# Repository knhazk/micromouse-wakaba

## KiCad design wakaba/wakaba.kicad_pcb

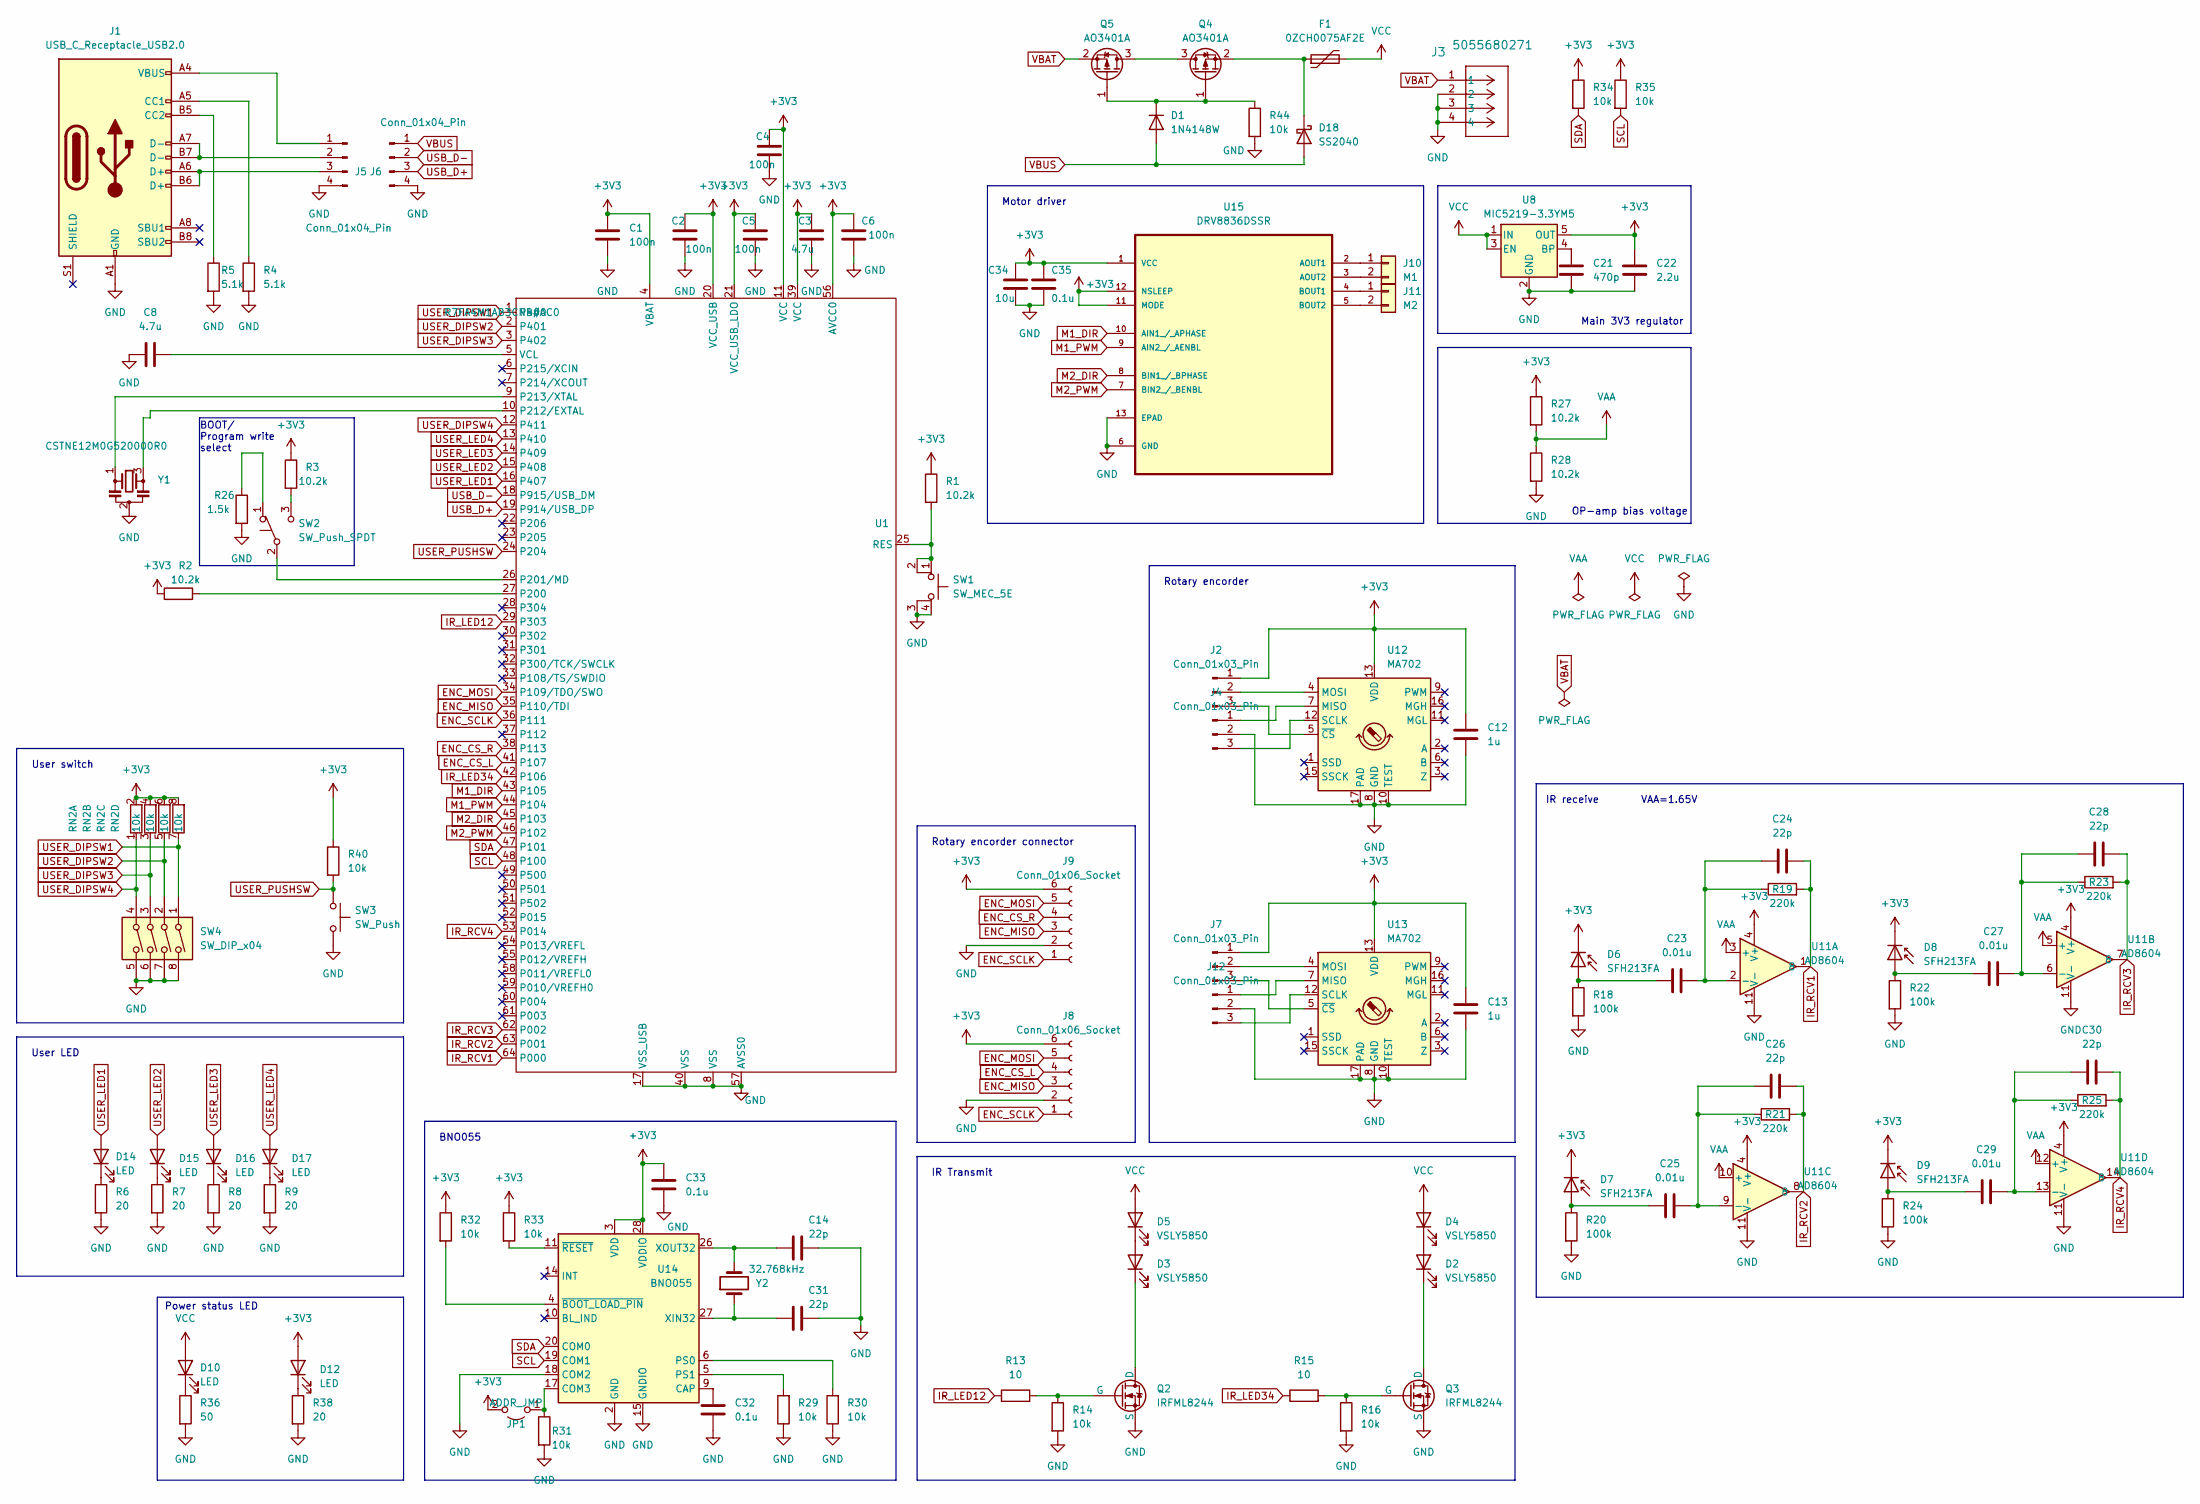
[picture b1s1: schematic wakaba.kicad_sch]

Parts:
C1, C2, C4, C5, C6: 100n; C_0603_1608Metric_Pad1.08x0.95mm_HandSolder
C3, C8: 4.7u; C_0805_2012Metric_Pad1.18x1.45mm_HandSolder
C12, C13: 1u; C_0603_1608Metric_Pad1.08x0.95mm_HandSolder
C14, C24, C26, C28, C30, C31: 22p; C_0603_1608Metric_Pad1.08x0.95mm_HandSolder
C21: 470p; C_0603_1608Metric_Pad1.08x0.95mm_HandSolder
C22: 2.2u; C_0603_1608Metric_Pad1.08x0.95mm_HandSolder
C23, C25, C27, C29: 0.01u; C_0603_1608Metric_Pad1.08x0.95mm_HandSolder
C32, C33, C35: 0.1u; C_0603_1608Metric_Pad1.08x0.95mm_HandSolder
C34: 10u; C_0603_1608Metric_Pad1.08x0.95mm_HandSolder
D1: 1N4148W; D_SOD-123
D2, D3, D4, D5: VSLY5850; LED_D5.0mm_Horizontal_O1.27mm_Z3.0mm
D6, D7, D8, D9: SFH213FA; LED_D5.0mm_Horizontal_O1.27mm_Z3.0mm
D10, D12, D14, D15, D16, D17: LED; LED_0603_1608Metric_Pad1.05x0.95mm_HandSolder
D18: SS2040; D_SOD-123F
F1: 0ZCH0075AF2E; R_1210_3225Metric_Pad1.30x2.65mm_HandSolder
J1: USB_C_Receptacle_USB2.0; USB_C_Receptacle_G-Switch_GT-USB-7010ASV
J2, J4, J7, J12: Conn_01x03_Pin; vertical_pcb_conn
J3: 5055680271; CON_5055680271
J5: Conn_01x04_Pin; pogo_usb
J6: Conn_01x04_Pin; pogopad_usb
J8, J9: Conn_01x06_Socket; vertical_pcb_conn_base
J10: M1; PinHeader_1x02_P1.27mm_Vertical
J11: M2; PinHeader_1x02_P1.27mm_Vertical
JP1: ADDR_JMP; SolderJumper-2_P1.3mm_Open_RoundedPad1.0x1.5mm
Q2, Q3: IRFML8244; SOT-23
Q4, Q5: AO3401A; SOT-23
R1, R2, R3, R27, R28: 10.2k; R_0603_1608Metric_Pad0.98x0.95mm_HandSolder
R4, R5: 5.1k; R_0603_1608Metric_Pad0.98x0.95mm_HandSolder
R6, R7, R8, R9, R38: 20; R_0603_1608Metric_Pad0.98x0.95mm_HandSolder
R13, R15: 10; R_0603_1608Metric_Pad0.98x0.95mm_HandSolder
R14, R16, R29, R30, R31, R32, R33, R34, R35, R40, R44: 10k; R_0603_1608Metric_Pad0.98x0.95mm_HandSolder
R18, R20, R22, R24: 100k; R_0603_1608Metric_Pad0.98x0.95mm_HandSolder
R19, R21, R23, R25: 220k; R_0603_1608Metric_Pad0.98x0.95mm_HandSolder
R26: 1.5k; R_0603_1608Metric_Pad0.98x0.95mm_HandSolder
R36: 50; R_0603_1608Metric_Pad0.98x0.95mm_HandSolder
RN2: 10k; R_Array_Concave_4x0402
SW1: SW_MEC_5E; SW_SPST_PTS810
SW2: SW_Push_SPDT; SSAJ120
SW3: SW_Push; SW_SPST_PTS810
SW4: SW_DIP_x04; SW_DIP_SPSTx04_Slide_Copal_CHS-04B_W7.62mm_P1.27mm
U1: R7FA4M1AB3CNB#AC0; QFN-64-1EP_8x8mm_P0.4mm_EP6.5x6.5mm
U8: MIC5219-3.3YM5; SOT-23-5
U11: AD8604; TSSOP-14_4.4x5mm_P0.65mm
U12, U13: MA702; QFN-16-1EP_3x3mm_P0.5mm_EP1.75x1.75mm
U14: BNO055; LGA-28_5.2x3.8mm_P0.5mm
U15: DRV8836DSSR; SON50P200X300X80-13N; MPN DRV8836DSSR; DigiKey_Part_Number 296-30392-2-ND
Y1: CSTNE12M0G520000R0; Resonator_SMD_Murata_CSTxExxV-3Pin_3.0x1.1mm
Y2: 32.768kHz; Crystal_SMD_2012-2Pin_2.0x1.2mm_HandSoldering

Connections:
+3V3: C1.1, C2.1, C3.1, C4.1, C5.1, C6.1, C12.1, C13.1, C22.1, C33.1, C34.1, C35.1, D6.1 (K), D7.1 (K), D8.1 (K), D9.1 (K), D12.2 (A), J2.1, J7.1, J8.6, J9.6, JP1.2 (B), R1.1, R2.1, R3.1, R27.1, R32.1, R33.1, R34.1, R35.1, R40.1, RN2.2 (R1.2), RN2.4 (R2.2), RN2.6 (R3.2), RN2.8 (R4.2), U1.4 (VBAT), U1.11 (VCC), U1.20 (VCC_USB), U1.21 (VCC_USB_LDO), U1.39 (VCC), U1.56 (AVCC0), U8.5 (OUT), U11.4 (V+), U12.13 (VDD), U13.13 (VDD), U14.3 (VDD), U14.28 (VDDIO), U15.1 (VCC), U15.11 (MODE), U15.12 (NSLEEP)
ENC_CS_L: J8.4, U1.41 (P107)
ENC_CS_R: J9.4, U1.38 (P113)
ENC_MISO: J8.3, J9.3, U1.35 (P110/TDI)
ENC_MOSI: J8.5, J9.5, U1.34 (P109/TDO/SWO)
ENC_SCLK: J8.1, J9.1, U1.36 (P111)
IR_LED12: R13.1, U1.29 (P303)
IR_LED34: R15.1, U1.42 (P106)
IR_RCV1: C24.2, R19.2, U1.64 (P000), U11.1 (8)
IR_RCV2: C26.2, R21.2, U1.63 (P001), U11.8
IR_RCV3: C28.2, R23.2, U1.62 (P002), U11.7 (8)
IR_RCV4: C30.2, R25.2, U1.53 (P014), U11.14 (8)
M1_DIR: U1.43 (P105), U15.10 (AIN1_/_APHASE)
M1_PWM: U1.44 (P104), U15.9 (AIN2_/_AENBL)
M2_DIR: U1.45 (P103), U15.8 (BIN1_/_BPHASE)
M2_PWM: U1.46 (P102), U15.7 (BIN2_/_BENBL)
unnamed: D1.1 (K), Q4.1 (G), Q5.1 (G), R44.1
unnamed: D2.2 (A), D4.1 (K)
unnamed: D2.1 (K), Q3.1 (D)
unnamed: D3.2 (A), D5.1 (K)
unnamed: D3.1 (K), Q2.1 (D)
unnamed: C23.1, D6.2 (A), R18.1
unnamed: C25.1, D7.2 (A), R20.1
unnamed: C27.1, D8.2 (A), R22.1
unnamed: C29.1, D9.2 (A), R24.1
unnamed: D10.1 (K), R36.1
unnamed: D12.1 (K), R38.1
unnamed: D14.1 (K), R6.1
unnamed: D15.1 (K), R7.1
unnamed: D16.1 (K), R8.1
unnamed: D17.1 (K), R9.1
unnamed: D18.1 (K), F1.1, Q4.2 (S)
unnamed: J1.A5 (CC1), R4.1
unnamed: J1.B5 (CC2), R5.1
unnamed: J2.2, U12.4 (MOSI)
unnamed: J2.3, U12.5 (~CS)
unnamed: J4.1, U12.7 (MISO)
unnamed: J4.3, U12.12 (SCLK)
unnamed: J1.A4 (VBUS), J1.A9 (VBUS), J1.B4 (VBUS), J1.B9 (VBUS), J5.1
unnamed: J1.A7 (D-), J1.B7 (D-), J5.2
unnamed: J1.A6 (D+), J1.B6 (D+), J5.3
unnamed: J7.2, U13.4 (MOSI)
unnamed: J7.3, U13.5 (~CS)
unnamed: J10.1, U15.2 (AOUT1)
unnamed: J10.2, U15.3 (AOUT2)
unnamed: J11.1, U15.4 (BOUT1)
unnamed: J11.2, U15.5 (BOUT2)
unnamed: J12.1, U13.7 (MISO)
unnamed: J12.3, U13.12 (SCLK)
unnamed: JP1.1 (A), R31.1, U14.17 (COM3)
unnamed: Q2.2 (G), R13.2, R14.1
unnamed: Q3.2 (G), R15.2, R16.1
unnamed: Q4.3 (D), Q5.3 (D)
unnamed: R26.1, SW2.1 (A)
unnamed: SW2.2 (B), U1.26 (P201/MD)
unnamed: R3.2, SW2.3 (C)
unnamed: R2.2, U1.27 (P200)
unnamed: U1.10 (P212/EXTAL), Y1.3
unnamed: U1.9 (P213/XTAL), Y1.1
unnamed: C8.2, U1.5 (VCL)
unnamed: C21.1, U8.4 (BP)
unnamed: C23.2, C24.1, R19.1, U11.2 (-)
unnamed: C27.2, C28.1, R23.1, U11.6 (-)
unnamed: C25.2, C26.1, R21.1, U11.9 (-)
unnamed: C29.2, C30.1, R25.1, U11.13 (-)
unnamed: C32.1, U14.9 (CAP)
unnamed: R30.2, U14.6 (PS0)
unnamed: R29.2, U14.5 (PS1)
unnamed: C31.1, U14.27 (XIN32), Y2.1
unnamed: C14.1, U14.26 (XOUT32), Y2.2
unnamed: R32.2, U14.4 (~BOOT_LOAD_PIN)
unnamed: R33.2, U14.11 (~RESET)
SCL: R35.2, U1.48 (P100), U14.19 (COM1)
SDA: R34.2, U1.47 (P101), U14.20 (COM0)
USB_D+: J6.3, U1.19 (P914/USB_DP)
USB_D-: J6.2, U1.18 (P915/USB_DM)
USER_DIPSW1: RN2.7 (R4.1), SW4.1, U1.1 (P400)
USER_DIPSW2: RN2.5 (R3.1), SW4.2, U1.2 (P401)
USER_DIPSW3: RN2.3 (R2.1), SW4.3, U1.3 (P402)
USER_DIPSW4: RN2.1 (R1.1), SW4.4, U1.12 (P411)
USER_LED1: D14.2 (A), U1.16 (P407)
USER_LED2: D15.2 (A), U1.15 (P408)
USER_LED3: D16.2 (A), U1.14 (P409)
USER_LED4: D17.2 (A), U1.13 (P410)
USER_PUSHSW: R40.2, SW3.1, U1.24 (P204)
VAA: R27.2, R28.1, U11.3 (+), U11.5 (+), U11.10 (+), U11.12 (+)
VBAT: J3.1, Q5.2 (S)
VBUS: D1.2 (A), D18.2 (A), J6.1
VCC: D4.2 (A), D5.2 (A), D10.2 (A), F1.2, U8.1 (IN), U8.3 (EN)

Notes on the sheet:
Rotary encorder
Main 3V3 regulator
Motor driver
Power status LED
User switch
IR Transmit
BNO055
User LED
BOOT/ Program write select
IR receive
OP-amp bias voltage
Rotary encorder connector
VAA=1.65V

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
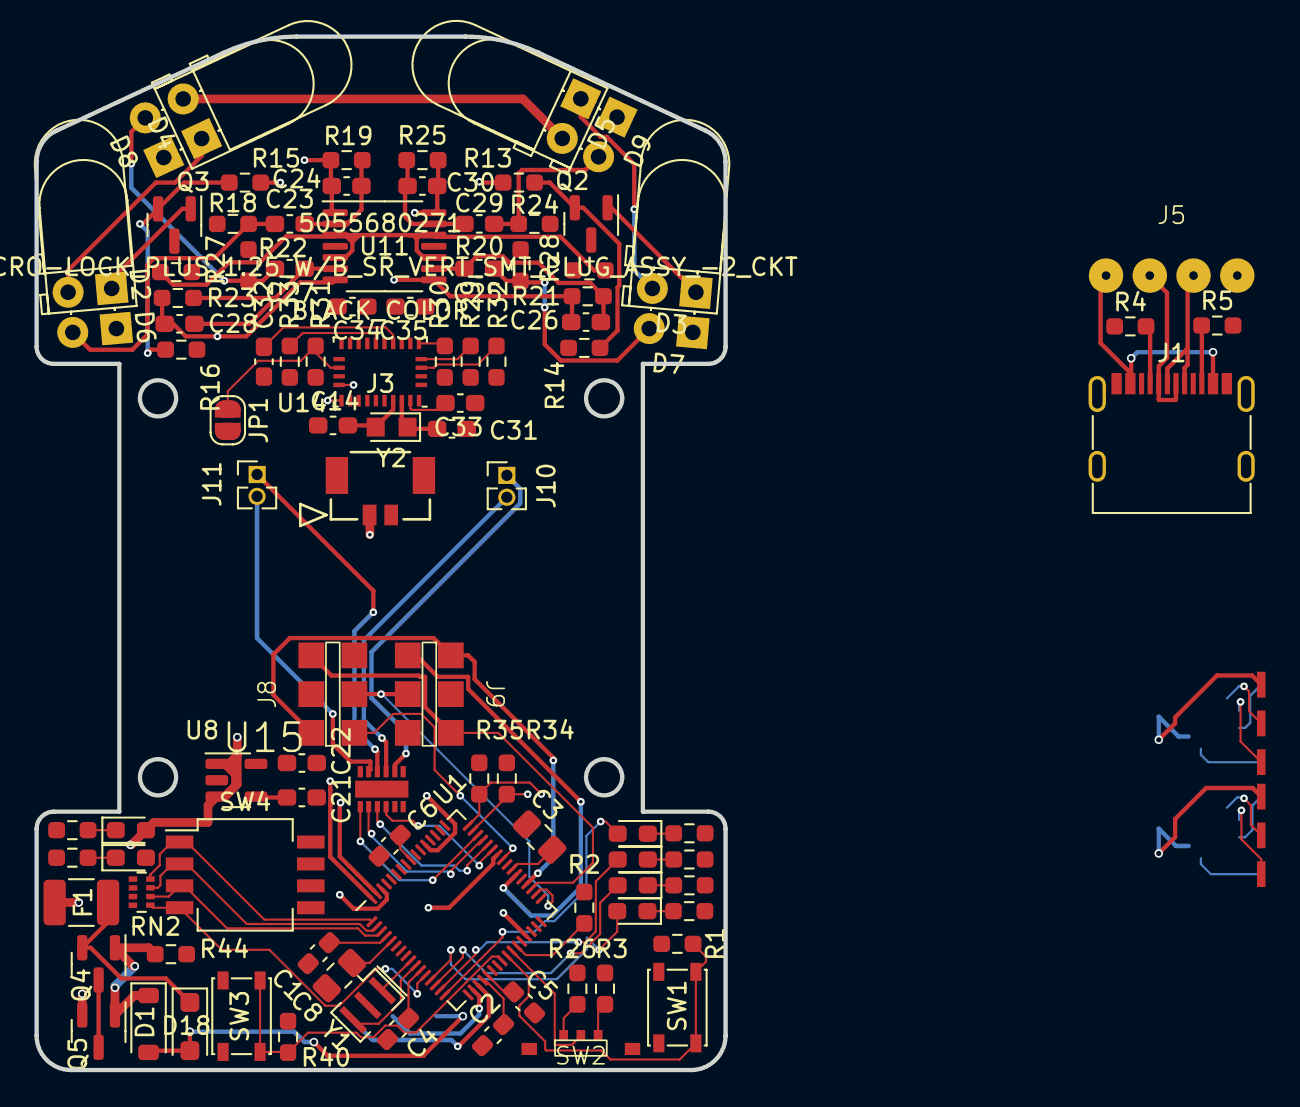
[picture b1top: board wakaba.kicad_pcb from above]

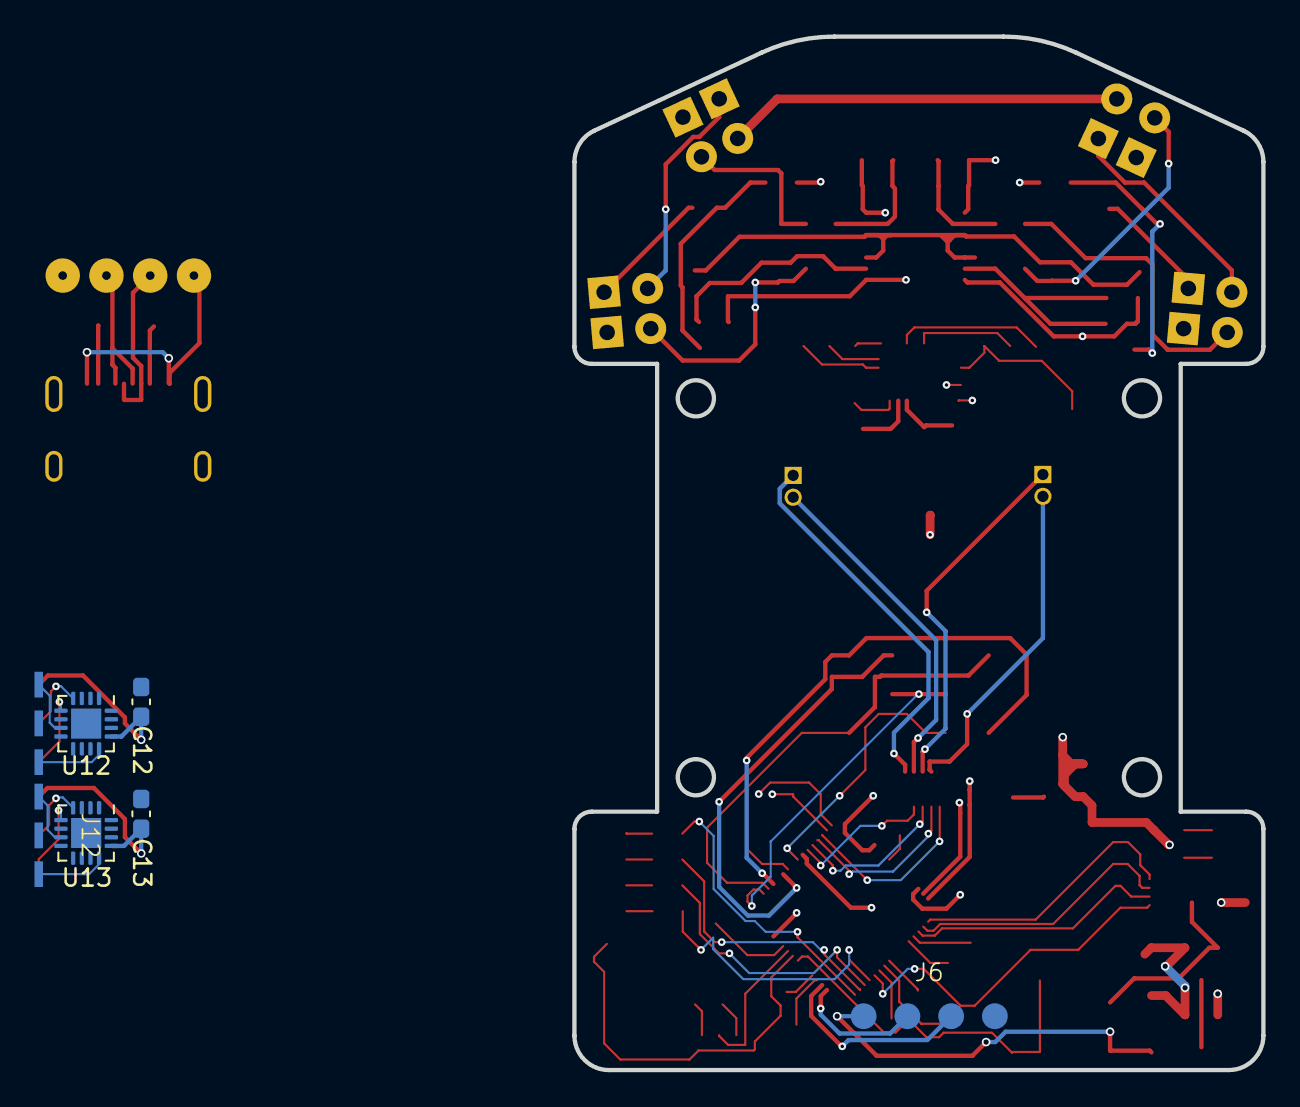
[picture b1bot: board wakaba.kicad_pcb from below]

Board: 4 copper layers, 40.0 x 60.0 mm, 108 parts (7 on the bottom side), 91 nets.

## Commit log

2023-09-23 とりあえず完成
2023-09-27 3v3に統一作業WIP
2023-11-10 kossanレビュー後修正WIP
2023-11-10 保護回路削除
2023-11-14 パターン一旦完成
2023-11-19 一旦線引き完了
